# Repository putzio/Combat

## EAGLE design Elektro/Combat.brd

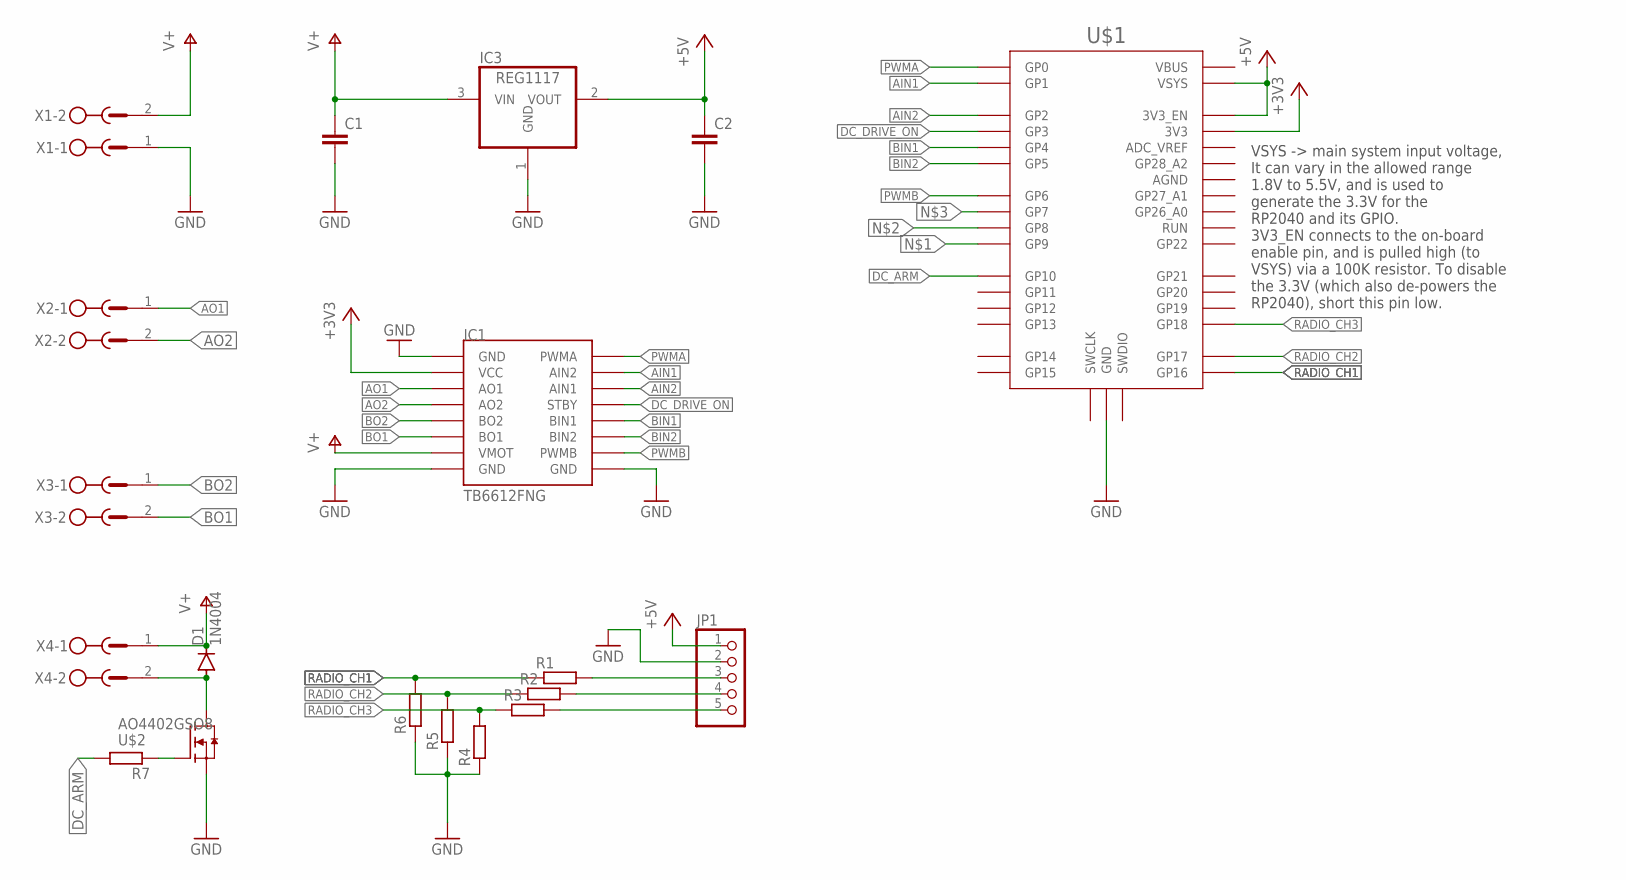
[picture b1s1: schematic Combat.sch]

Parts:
C1, C2: C-EUC1206; C1206
D1: 1N4004; DO41-10
IC1: MODUL_POLOLU
IC3: REG1117; SOT223
JP1: PINHD-1X5; 1X05
R1, R2, R3, R4, R6, R7: R-EU_R1206; R1206
R5: R-EU_0204/7; 0204/7
U$1: RPI_PICO-TH; RPI_PICO_TH
U$2: AO4402GSO8; SO8
X1, X2, X3, X4: MSTBV2

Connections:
+3V3: IC1.VCC, U$1.3V3
+5V: C2.1, IC3.2 (VOUT), JP1.1, U$1.3V3_EN, U$1.VSYS
AIN1: IC1.AIN2, U$1.GP1
AIN2: IC1.AIN1, U$1.GP2
AO1: IC1.AO1, X2.1
AO2: IC1.A02 (AO2), X2.2
BIN1: IC1.BIN1, U$1.GP4
BIN2: IC1.BIN2, U$1.GP5
BO1: IC1.BO1, X3.2
BO2: IC1.BO2, X3.1
DC_ARM: R7.2, U$1.GP10
DC_DRIVE_ON: IC1.STBY, U$1.GP3
GND: C1.2, C2.2, IC1.GND1 (GND), IC1.GND2 (GND), IC1.GND3 (GND), IC3.1 (GND), JP1.2, R4.1, R5.1, R6.1, U$1.GND@1 (GND), U$1.GND@2 (GND), U$1.GND@3 (GND), U$1.GND@4 (GND), U$1.GND@5 (GND), U$1.GND@6 (GND), U$1.GND@7 (GND), U$1.GND@8 (GND), U$2.1 (S), U$2.2 (S), U$2.3 (S), X1.1
unnamed: JP1.3, R1.2, U$1.GP9
unnamed: JP1.4, R2.2, U$1.GP8
unnamed: JP1.5, R3.2, U$1.GP7
unnamed: D1.A, U$2.5 (D), U$2.6 (D), U$2.7 (D), U$2.8 (D), X4.2
unnamed: R7.1, U$2.4 (G)
PWMA: IC1.PWMA, U$1.GP0
PWMB: IC1.PWMB, U$1.GP6
RADIO_CH1: R1.1, R6.2, U$1.GP16
RADIO_CH2: R2.1, R5.2, U$1.GP17
RADIO_CH3: R3.1, R4.2, U$1.GP18
V+: C1.1, D1.C, IC1.VMOT, IC3.3 (VIN), X1.2, X4.1

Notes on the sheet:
VSYS -> main system input voltage, It can vary in the allowed range 1.8V to 5.5V, and is used to generate the 3.3V for the RP2040 and its GPIO. 3V3_EN connects to the on-board enable pin, and is pulled high (to VSYS) via a 100K resistor. To disable the 3.3V (which also de-powers the RP2040), short 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

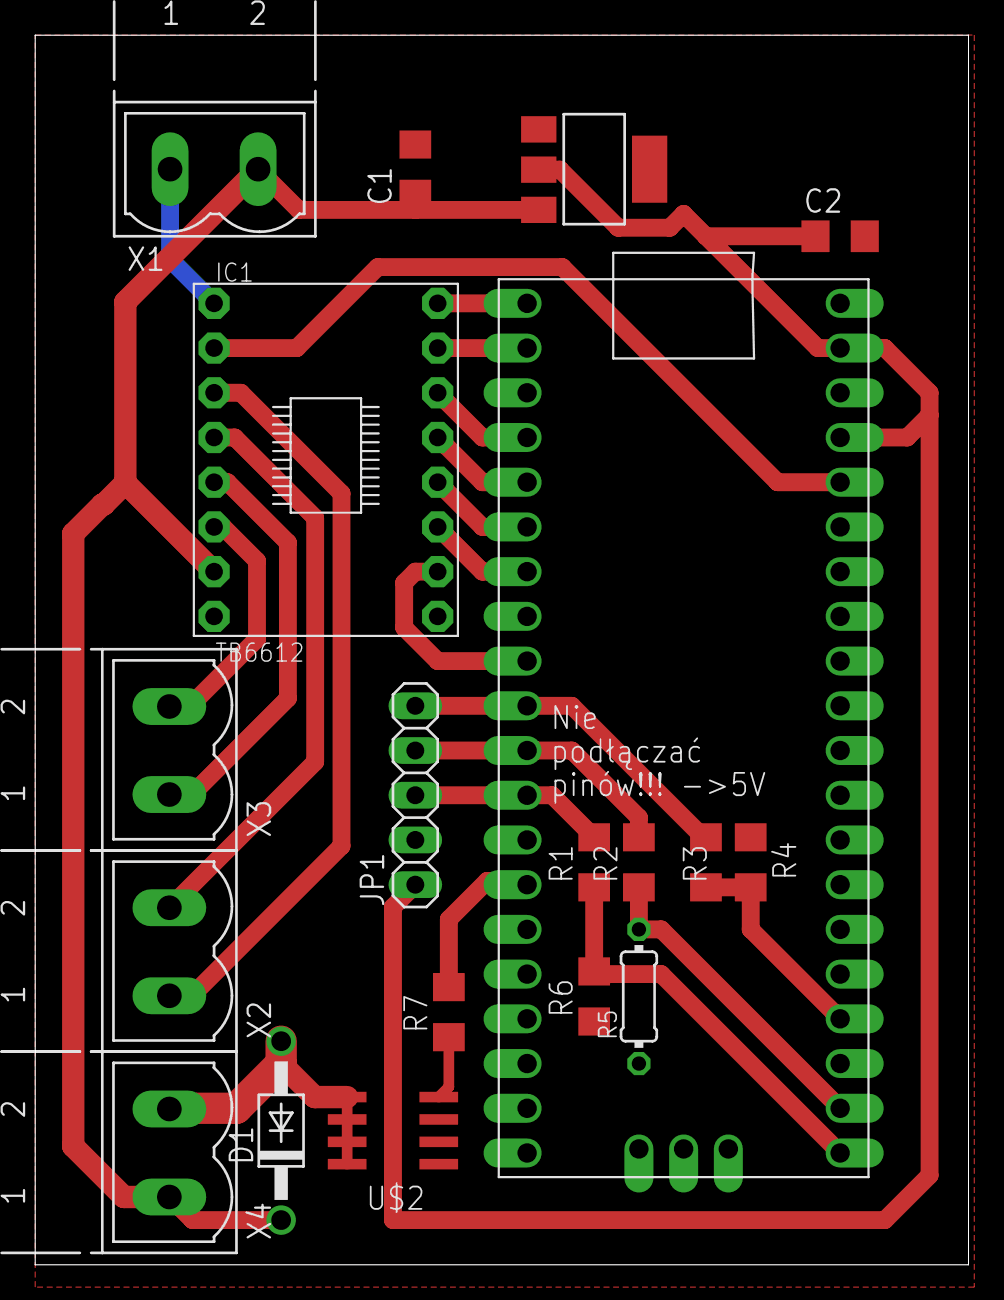
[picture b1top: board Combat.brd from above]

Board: 2 copper layers, 53.0 x 69.8 mm, 19 parts (0 on the bottom side), 24 nets.

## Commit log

2022-06-09 Init commit
2022-06-09 Electronics (.sch, .brd)
2022-06-09 making board smaller, SMD capacitators
